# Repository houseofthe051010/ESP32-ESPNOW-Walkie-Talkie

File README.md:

Source: 

## The Project

This is a ESP32 walkie talkie that uses WIFi (ESPNOW) for long range communication. It uses the esp32-wroom-32-U with an external U.fl connector, OLED 0.96 I2C display, I2S INMP441 microphone, I2S MAX98357A 3W speaker amplifier, 10k volume potentiometer, PTT button + 5 menu buttons, LASER, and LED. The aim of this walkie talkie was to not just serve as a walkie talkie, but sort of like a custom flipper zero that was more wireless oriented, although the walkie talkie comes with 3 female dupont pins that can be plugged in externally for a UART connection.

This device was framed as a walkie talkie but it can be used as a Wi-Fi/IoT device handheld controller platform. This is the main advantage with WIFI on esp32s as you can connect to a lot of places.

### Features

* ESP-NOW DIRECT VOICE (No router needed, multiple devices can connect)
* U.FL antenna for maximum range
* Tested to 600 meters of distance
* No acknowledge on ESPNOW, just shout and listen
* 16 kHz mono voice capture with IMA ADPCM compression
* No acknowledgement can be a problem with dropped packets so at weak ranges packets are automatically duplicated
* Built in black box logging with telemetry that can be uploaded to computer.
* OLED GUI with many features to control the walkie talkie and use as a remote for other wifi things.

## Walkie Talkie Hardware

The enclosure was designed to have enough space to solder every wire, but a custom PCB version was also made, scroll all the way down to learn more about fabricating PCB.

### Electronics

* ESP32WROOM32 U.FL
* OLED I2C 0.96'
* I2S INMP441 MIC
* 10K Volume potentiometer.
* 2000 MAH LIPO
* 6 push buttons
* 5mm LED light
* 5V laser module
* Voltage divider for ADC battery voltage measurment
* Main power switch

## Assembly Process

### 1. Printed enclosure

All these parts contribute to the final product

* [`walkie_talkie_bottom_case.stl`](SOURCE%20CAD/INDIVIDUAL%20STLS/walkie_talkie_bottom_case.stl)
* [`walkie_talkie_top_cover.stl`](SOURCE%20CAD/INDIVIDUAL%20STLS/walkie_talkie_top_cover.stl)
* [`walkie_talkie_top_buttons_grid.stl`](SOURCE%20CAD/INDIVIDUAL%20STLS/walkie_talkie_top_buttons_grid.stl)
* [`walkie_talkie_OK_button.stl`](SOURCE%20CAD/INDIVIDUAL%20STLS/walkie_talkie_OK_button.stl)
* [`walkie_talkie_PTT_button.stl`](SOURCE%20CAD/INDIVIDUAL%20STLS/walkie_talkie_PTT_button.stl)
* [`walkie_talkie_PTT_button_insert.stl`](SOURCE%20CAD/INDIVIDUAL%20STLS/walkie_talkie_PTT_button_insert.stl)

### 2. Power system

The battery powers the TP4056 which gives power to a boost converter than powers the entire device

1. Wire th TP4056 through the battery to the main switch to the boost convert and then to the esp32 VIN rail.

### 3. Electronics wiring

1. To make it easy and not messy, wire every component listed in the schematic to their respected GPIO and some pins might have multiple wires to them, thats fine.
2. Make sure to use heat shrink tape to avoid short circuits. 

### 4. Front-panel assembly

1. The LED and laser press into their  holes.
2. The PTT, OK, and four navigation buttons sit in the front-panel openings.
3. Insert the OLED
4. Secure all with super glue. Make sure to apply around perimeter and not damage the electronics.

### 5. Internal packing

1. Insert the electronics. One at a type, placing the esp32 underneath the TP4056 mount, and glueing each part to their holes.
2. The enclosure has enough space to accodomate addition UART connections if you want to connect something else later on.

### 6. ESP-IDF firmware loading

1. Fork the project and config with ESP-IDF to upload the code
2. Make sure you have experience with using powershell, open it

3. Init the powershell

   ```powershell
   idf.py set-target esp32
   ```

4. Open project using

   ```powershell
   idf.py menuconfig
   ```

6. Compile using

   ```powershell
   idf.py build
   ```

7. Flash using

   ```powershell
   idf.py flash monitor
   ```

## Circuit Diagram

### Device PINOUT (Use when soldering)

| Function             | ESP32 GPIO |
| -------------------- | ---------: |
| OLED SCL             |     GPIO18 |
| OLED SDA             |     GPIO19 |
| Speaker BCLK         |     GPIO32 |
| Speaker WS/LRC       |     GPIO33 |
| Speaker DIN          |     GPIO25 |
| Microphone BCLK      |     GPIO16 |
| Microphone WS        |     GPIO17 |
| Microphone SD        |      GPIO4 |
| OK button            |      GPIO0 |
| Bottom-left button   |     GPIO14 |
| Bottom-right button  |     GPIO15 |
| Laser                |     GPIO21 |
| Volume potentiometer |     GPIO34 |
| Battery divider      |     GPIO35 |

## My versions:

## Grey Walkie

This is my 2nd iteration with much cleaner wiring

## Black Walkie

This first iteration is much more messier

### User Interface

The user interface has a whole "apps" menu for different wifi connections and button use cases, you can code your own for your own custom use cases.

### Black Box

You can debug or see what happend with the walkie in the field, this isn't really needed now that I have perfected the code though, but can be helpful if you're making your own changes.

Example of a JSON black box record:

```json
{"event":"radio_stats","t_ms":123456,"board":"BLACK","ch":1,"ptt":false,"link":true,"rssi_dbm":-82,"quality_pct":21,"jitter_frames":3,"vol_pct":50,"tx_audio":0,"tx_audio_dup":0,"tx_ctrl":2,"tx_no_mem":0,"tx_fail":0,"rx_audio":48,"rx_audio_dup":7,"rx_audio_old":0,"rx_plc":2,"rx_ctrl":1,"rx_wrong_peer":0,"rx_bad_proto":0,"rx_wrong_channel":0}
```

## Bill of Materials

| Category    | Quantity | Part                                 | Purchase Link                                                      | Estimated Price |
| ----------- | -------: | ------------------------------------ | ------------------------------------------------------------------ | --------------: |
| Fabricated  |        2 | Walkie-talkie enclosure              | [AliExpress](https://www.aliexpress.us/item/3256806989098121.html) |           $2.22 |
| Electronics |        2 | ESP32 development board              | [AliExpress](https://www.aliexpress.us/item/3256807617923920.html) |           $1.90 |
| Radio       |        2 | External antenna                     | [AliExpress](https://www.aliexpress.us/item/3256812004598286.html) |      $0.64 used |
| Display     |        2 | 0.96-inch OLED display               | [AliExpress](https://www.aliexpress.us/item/3256805954920554.html) |      $1.98 used |
| Audio       |        2 | I2S microphone                       | [AliExpress](https://www.aliexpress.us/item/3256810210666726.html) |           $6.45 |
| Audio       |        2 | I2S speaker amplifier                | [AliExpress](https://www.aliexpress.us/item/3256809715431644.html) |      $1.88 used |
| Audio       |        2 | Speaker                              | [AliExpress](https://www.aliexpress.us/item/3256805151989671.html) |           $0.99 |
| Control     |        2 | Volume potentiometer                 | [AliExpress](https://www.aliexpress.us/item/3256805703535495.html) |           $0.99 |
| Power       |        2 | Lithium battery                      | [AliExpress](https://www.aliexpress.us/item/3256811489152615.html) |     $10.96 used |
| Power       |        2 | Battery charger and protection board | [AliExpress](https://www.aliexpress.us/item/3256809139500038.html) |      $0.20 used |
| Power       |        2 | Boost converter                      | [AliExpress](https://www.aliexpress.us/item/3256811757076890.html) |      $1.88 used |
| Power       |        2 | Main power switch                    | [AliExpress](https://www.aliexpress.us/item/3256809823421130.html) |           $2.37 |
| Lighting    |        2 | Status LED                           | [AliExpress](https://www.aliexpress.us/item/3256807537207911.html) |      $0.02 used |
| Lighting    |        2 | Laser module                         | [AliExpress](https://www.aliexpress.us/item/3256808318801769.html) |           $0.99 |
| Control     |       12 | Momentary pushbutton                 | [AliExpress](https://www.aliexpress.us/item/3256810479380665.html) |           $0.99 |
| Optional RC |        2 | Continuous-rotation servo            | [AliExpress](https://www.aliexpress.us/item/3256804365417662.html) |           $9.28 |
| Measurement |        2 | 100 kΩ battery-divider resistor      | [AliExpress](https://www.aliexpress.us/item/3256802303553096.html) |      $0.02 used |
| Measurement |        2 | 220 kΩ battery-divider resistor      | [AliExpress](https://www.aliexpress.us/item/3256802303553096.html) |      $0.02 used |
| Wiring      |        1 | Signal and power wire                | [AliExpress](https://www.aliexpress.us/item/3256810394181790.html) | $0.99 allowance |

## Custom PCB Fabrication Option

If you want to avoid the hassle of soldering than fabricate your own PCB here: 

See [CUSTOM PCB FABRICATION/README.md](CUSTOM%20PCB%20FABRICATION/README.md) for the JLBPCB fabrication guide

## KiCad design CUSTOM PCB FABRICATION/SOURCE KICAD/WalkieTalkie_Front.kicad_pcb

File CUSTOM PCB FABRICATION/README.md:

# Custom PCB Fabrication

This is a KiCad PCB for those looking to make the walkie talkie from PCBs. Note that you will still have to solder some components.

## PCB Preview

Main board:

Front/user-interface board:

## Risks

Although this custom PCB works, I will be manufactering a redesigned much cleaner version later that avoids the hassle of 2 PCB boards and does everything one one, with a much slimmer walkie talkie design.

## Manufacturer Files

In this folder are the source kicad files for the PCB and manufacterable GERBER files.

### Main PCB

- [Gerber/drill ZIP](MANUFACTOR%20FILES/MAIN%20PCB/WalkieTalkie_Main_Gerbers_Drill.zip)
- [JLCPCB BOM CSV](MANUFACTOR%20FILES/MAIN%20PCB/WalkieTalkie_Main_JLCPCB_BOM.csv)
- [JLCPCB CPL / position CSV](MANUFACTOR%20FILES/MAIN%20PCB/WalkieTalkie_Main_JLCPCB_CPL.csv)

### Front PCB

- [Gerber/drill ZIP](MANUFACTOR%20FILES/FRONT%20PCB/WalkieTalkie_Front_Gerbers_Drill.zip)
- [JLCPCB BOM CSV](MANUFACTOR%20FILES/FRONT%20PCB/WalkieTalkie_Front_JLCPCB_BOM.csv)
- [JLCPCB CPL / position CSV](MANUFACTOR%20FILES/FRONT%20PCB/WalkieTalkie_Front_JLCPCB_CPL.csv)

## Parts JLCPCB Can Usually Assemble

Most of the parts and SMD components should be assembled by JLBPCB but you will need to solder these parts:

- PTT Button
- Laser module
- 10K volume potentiometer
- OLED display
- Slim 3W speaker
- Battery
- Power switch

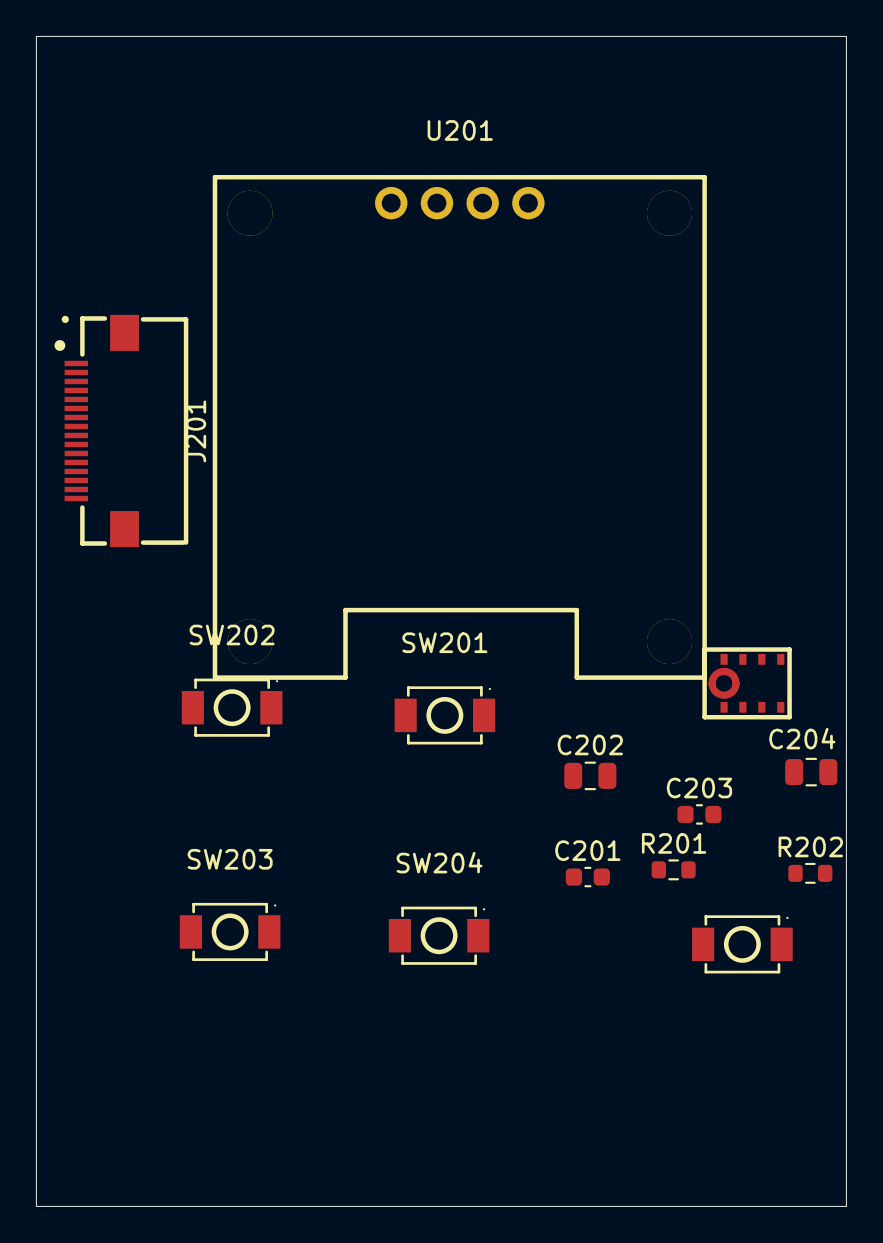
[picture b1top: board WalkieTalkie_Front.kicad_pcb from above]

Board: 2 copper layers, 45.0 x 65.0 mm, 14 parts (0 on the bottom side), 12 nets, no tracks yet.

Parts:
C201, C203: 100nF; C_0603_1608Metric
C202, C204: 10uF; C_0805_2012Metric
J201: MAIN BOARD FFC; FPC-SMD_P0.50-16P_FGS-XJ-H2.0
R201, R202: 4.7k; R_0603_1608Metric
SW201: OK; SW-SMD_L3.9-W3.0-P4.45
SW202: TOP LEFT; SW-SMD_L3.9-W3.0-P4.45
SW203: TOP RIGHT; SW-SMD_L3.9-W3.0-P4.45
SW204: BOTTOM LEFT; SW-SMD_L3.9-W3.0-P4.45
SW205: BOTTOM RIGHT; SW-SMD_L3.9-W3.0-P4.45
U201: HS96L03W2C03 0.96 OLED; OLED-TH_L27.8-W27.2-P2.54_C9900033791
U202: INMP441ACEZ; MID-SMD_L4.7-W3.8_INMP441ACEZ

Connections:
/+3V3: C201.2, C202.2, C203.2, C204.2, J201.2, J201.15, R201.2, R202.2, U201.2 (VCC), U202.7 (VDD), U202.8 (CHIPEN)
/BTN_TOP_LEFT: J201.10, SW202.1
/BTN_TOP_RIGHT: J201.11, SW203.1
/GND: C201.1, C202.1, C203.1, C204.1, J201.1, J201.3, J201.14, J201.16, J201.17, J201.18, SW201.2, SW202.2, SW203.2, SW204.2, SW205.2, U201.1 (GND), U202.4 (L/R), U202.5 (GND), U202.6 (GND), U202.9 (GND)
/GPIO0_BTN_OK: J201.9, SW201.1
/GPIO4_MIC_SD: J201.8, U202.2 (SD)
/GPIO14_BTN_BOTTOM_LEFT: J201.12, SW204.1
/GPIO15_BTN_BOTTOM_RIGHT: J201.13, SW205.1
/GPIO16_MIC_BCLK: J201.6, U202.1 (SCK)
/GPIO17_MIC_WS: J201.7, U202.3 (WS)
/GPIO18_OLED_SCL: J201.4, R201.1, U201.3 (SCL)
/GPIO19_OLED_SDA: J201.5, R202.1, U201.4 (SDA)

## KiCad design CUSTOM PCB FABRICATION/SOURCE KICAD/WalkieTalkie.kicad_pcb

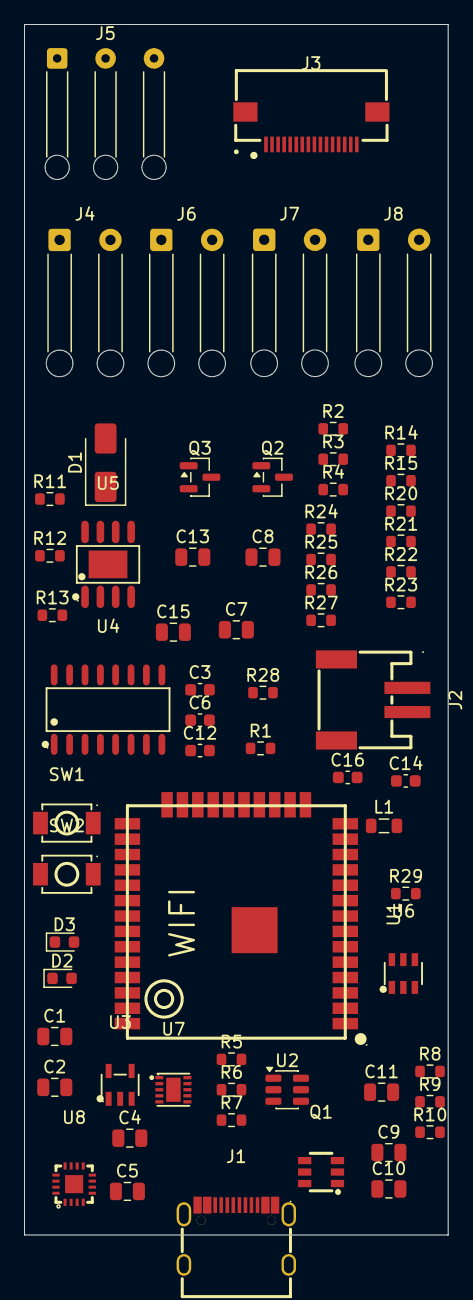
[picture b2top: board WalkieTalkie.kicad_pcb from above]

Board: 2 copper layers, 35.0 x 100.0 mm, 66 parts (0 on the bottom side), 57 nets, no tracks yet.

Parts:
C1, C2, C11: 1uF; C_0805_2012Metric
C3, C6, C12, C14, C16: 100nF; C_0603_1608Metric
C4, C5, C7, C8, C9, C10, C13, C15: 10uF; C_0805_2012Metric
D1: SS34; D_SMA
D2: RED CHARGING; LED_0603_1608Metric
D3: GREEN FULL; LED_0603_1608Metric
J1: TYPE-C-31-M-12; USB-C_SMD-TYPE-C-31-M-12_1
J2: BATTERY JST-PH; CONN-SMD_P2.00_S2B-PH-SM4-TB-LF-SN
J3: FRONT BOARD FFC; FPC-SMD_P0.50-16P_FGS-XJ-H2.0
J4: SPEAKER WIRES; SolderWire-0.25sqmm_1x02_P4.2mm_D0.65mm_OD1.7mm_Relief
J5: 10k POTENTIOMETER; SolderWire-0.15sqmm_1x03_P4mm_D0.5mm_OD1.5mm_Relief
J6: PTT BUTTON; SolderWire-0.25sqmm_1x02_P4.2mm_D0.65mm_OD1.7mm_Relief
J7: EXTERNAL LED; SolderWire-0.25sqmm_1x02_P4.2mm_D0.65mm_OD1.7mm_Relief
J8: LASER WIRES; SolderWire-0.25sqmm_1x02_P4.2mm_D0.65mm_OD1.7mm_Relief
L1: 2.2uH >=2A; L_0805_2012Metric
Q1: FS8205A; SOT-23-6_L2.9-W1.6-P0.95-LS2.8-BR
Q2: AO3401A; SOT-23
Q3: AO3400A; SOT-23
R1, R2: 5.1k; R_0603_1608Metric
R3: 2.4k (500mA); R_0603_1608Metric
R4, R5, R7: 1k; R_0603_1608Metric
R6: 100R; R_0603_1608Metric
R8, R10, R11: 10k; R_0603_1608Metric
R9, R12, R15: 100k; R_0603_1608Metric
R13: 1M; R_0603_1608Metric
R14: 330R; R_0603_1608Metric
R20, R21, R22, R23: 0R BLACK; R_0603_1608Metric
R24, R25, R26, R27: 0R GREY; R_0603_1608Metric
R28, R29: 220k; R_0603_1608Metric
SW1: RESET; SW-SMD_L3.9-W3.0-P4.45
SW2: BOOT; SW-SMD_L3.9-W3.0-P4.45
U1: ESP32-WROOM-32U-N4; WIFIM-SMD_38P-L19.2-W18.0-P1.27
U2: USBLC6-2SC6; SOT-23-6
U3: ME6211C33M5G-N; SOT-23-5_L3.0-W1.7-P0.95-LS2.8-BL
U4: CH340C; SOP-16_L10.0-W3.9-P1.27-LS6.0-BL
U5: TP4056; ESOP-8_L4.9-W3.9-P1.27-LS6.0-BL-EP-4
U6: DW01A; SOT-23-6_L2.9-W1.6-P0.95-LS2.8-BL
U7: TPS63031DSKR; SON-10_L2.5-W2.5-P0.50-TL-EP
U8: MAX98357AETE+T; TQFN-16_L3.0-W3.0-P0.50-BL-EP1.5

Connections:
/+3V3: C9.2, C10.2, C12.2, C13.2, J3.2, J3.15, J5.1, J8.1, R10.2, R11.2, U1.2 (3V3), U7.1 (VOUT), U7.10 (FB)
/+3V3_USB: C2.2, C3.2, U3.5 (VOUT), U4.4 (V3), U4.16 (VCC)
/AMP_GAIN: R12.2, U8.2 (GAIN_SLOT)
/AMP_SD_MODE: R13.2, U8.4 (~SD_MODE)
/BAT_POS: C5.2, J2.1, Q2.2 (S), R6.2, R28.2, U5.5 (BAT)
/BAT_RAW_N: C6.1, J2.2, Q1.1 (S1), U6.6 (GND)
/BB_L1: L1.2, U7.4 (L1)
/BB_L2: L1.1, U7.2 (L2)
/BTN_TOP_LEFT: J3.10, R22.1, R26.1
/BTN_TOP_RIGHT: J3.11, R23.1, R27.1
/DW_VCC: C6.2, R6.1, U6.5 (VCC)
/DW_VM: R7.2, U6.2 (VM)
/ESP_EN: C11.2, R10.1, SW1.1, U1.3 (EN)
/GND: C1.1, C2.1, C3.1, C4.1, C5.1, C7.1, C8.1, C9.1, C10.1, C11.1, C12.1, C13.1, C14.1, C15.1, C16.1, J1.1 (EH), J1.2 (EH), J1.3 (EH), J1.4 (EH), J1.A1B12 (GND), J1.B1A12 (GND), J2.3, J2.4, J3.1, J3.3, J3.14, J3.16, J3.17, J3.18, J5.3, J6.2, J7.2, Q1.3 (S2), Q3.2 (S), R1.1, R2.1, R3.1, R7.1, R9.1, R12.1, R15.1, R29.1, SW1.2, SW2.2, U1.1 (GND), U1.15 (GND), U1.38 (GND), U1.39 (GND), U2.2 (GND), U3.2 (VSS), U4.1 (GND), U4.15 (R232), U5.1 (TEMP), U5.3 (GND), U5.9 (PAD), U6.4 (TD), U7.3 (PGND), U7.7 (PS/SYNC), U7.9 (GND), U7.11 (EP), U8.3 (GND), U8.11 (GND), U8.15 (GND), U8.17 (EP)
/GPIO0_BTN_OK: J3.9, R11.1, SW2.1, U1.25 (IO0)
/GPIO2: R23.2, R26.2, U1.24 (IO2)
/GPIO4_MIC_SD: J3.8, U1.26 (IO4)
/GPIO14_BTN_BOTTOM_LEFT: J3.12, U1.13 (IO14)
/GPIO15_BTN_BOTTOM_RIGHT: J3.13, U1.23 (IO15)
/GPIO16_MIC_BCLK: J3.6, U1.27 (IO16)
/GPIO17_MIC_WS: J3.7, U1.28 (IO17)
/GPIO18_OLED_SCL: J3.4, U1.30 (IO18)
/GPIO19_OLED_SDA: J3.5, U1.31 (IO19)
/GPIO21_LASER: Q3.1 (G), R15.2, U1.33 (IO21)
/GPIO22: R20.2, R25.2, U1.36 (IO22)
/GPIO23: R21.2, R24.2, U1.37 (IO23)
/GPIO25_SPK_DIN: U1.10 (IO25), U8.1 (DIN)
/GPIO26: R22.2, R27.2, U1.11 (IO26)
/GPIO32_SPK_BCLK: U1.8 (IO32), U8.16 (BCLK)
/GPIO33_SPK_LRC: U1.9 (IO33), U8.14 (LRCLK)
/GPIO34_VOLUME: J5.2, U1.6 (IO34)
/GPIO35_BATTERY: C16.2, R28.1, R29.2, U1.7 (IO35)
/LASER_NEG: J8.2, Q3.3 (D)
/LED_CHRG_A: D2.1 (K), R4.1
/LED_CTRL: R14.2, R21.1, R25.1
/LED_DONE_A: D3.1 (K), R5.1
/LED_EXT_ANODE: J7.1, R14.1
/LOAD_GATE: Q2.1 (G), R8.1, R9.2
/MOS_MID: Q1.2 (D1/D2), Q1.5 (D1/D2)
/PROTECT_OC: Q1.4 (G2), U6.3 (OC)
/PROTECT_OD: Q1.6 (G1), U6.1 (OD)
/PTT: J6.1, R20.1, R24.1
/SPK_MINUS: J4.2, U8.10 (OUTN)
/SPK_PLUS: J4.1, U8.9 (OUTP)
/TP_CHRG: D2.2 (A), U5.7 (CHRG)
/TP_PROG: R3.2, U5.2 (PROG)
/TP_STDBY: D3.2 (A), U5.6 (STDBY)
/UART_RX0: U1.34 (RXD0), U4.2 (TXD)
/UART_TX0: U1.35 (TXD0), U4.3 (RXD)
/USB_CC1: J1.A5 (CC1), R1.2
/USB_CC2: J1.B5 (CC2), R2.2
/USB_DN: U2.6 (I/O1), U4.6 (D-)
/USB_DN_CONN: J1.A7 (DN1), J1.B7 (DN2), U2.1 (I/O1)
/USB_DP: U2.4 (I/O2), U4.5 (D+)
/USB_DP_CONN: J1.A6 (DP1), J1.B6 (DP2), U2.3 (I/O2)
/USB_VBUS: C1.2, C4.2, D1.2 (A), J1.A4B9 (VBUS), J1.B4A9 (VBUS), R4.2, R5.2, R8.2, U2.5 (VBUS), U3.1 (VIN), U3.3 (CE), U5.4 (VCC), U5.8 (CE)
/VSYS: C7.2, C8.2, C14.2, C15.2, D1.1 (K), Q2.3 (D), R13.1, U7.5 (VIN), U7.6 (EN), U7.8 (VINA), U8.7 (VDD), U8.8 (VDD)

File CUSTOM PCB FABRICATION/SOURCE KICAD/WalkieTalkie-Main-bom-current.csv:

"Refs","Value","Footprint","MPN","LCSC","DNP"
"C1,C2,C11","1uF","Capacitor_SMD:C_0805_2012Metric","","",""
"C3,C6,C12,C14,C16","100nF","Capacitor_SMD:C_0603_1608Metric","","",""
"C4,C5,C7-C10,C13,C15","10uF","Capacitor_SMD:C_0805_2012Metric","","",""
"D1","SS34","Diode_SMD:D_SMA","SS34","C8678",""
"D2","RED CHARGING","LED_SMD:LED_0603_1608Metric","","",""
"D3","GREEN FULL","LED_SMD:LED_0603_1608Metric","","",""
"J1","TYPE-C-31-M-12","WalkieTalkie_JLCPCB:USB-C_SMD-TYPE-C-31-M-12_1","TYPE-C-31-M-12","C165948",""
"J2","BATTERY JST-PH","WalkieTalkie_JLCPCB:CONN-SMD_P2.00_S2B-PH-SM4-TB-LF-SN","S2B-PH-SM4-TB(LF)(SN)","C295747",""
"J3","FRONT BOARD FFC","WalkieTalkie_JLCPCB:FPC-SMD_P0.50-16P_FGS-XJ-H2.0","AFC01-S16FCC-00","C262272",""
"J4","SPEAKER WIRES","Connector_Wire:SolderWire-0.25sqmm_1x02_P4.2mm_D0.65mm_OD1.7mm_Relief","","",""
"J5","10k POTENTIOMETER","Connector_Wire:SolderWire-0.15sqmm_1x03_P4mm_D0.5mm_OD1.5mm_Relief","","",""
"J6","PTT BUTTON","Connector_Wire:SolderWire-0.25sqmm_1x02_P4.2mm_D0.65mm_OD1.7mm_Relief","","",""
"J7","EXTERNAL LED","Connector_Wire:SolderWire-0.25sqmm_1x02_P4.2mm_D0.65mm_OD1.7mm_Relief","","",""
"J8","LASER WIRES","Connector_Wire:SolderWire-0.25sqmm_1x02_P4.2mm_D0.65mm_OD1.7mm_Relief","","",""
"L1","2.2uH >=2A","Inductor_SMD:L_0805_2012Metric","","",""
"Q1","FS8205A","WalkieTalkie_JLCPCB:SOT-23-6_L2.9-W1.6-P0.95-LS2.8-BR","FS8205A","C2830320",""
"Q2","AO3401A","Package_TO_SOT_SMD:SOT-23","AO3401A","C15127",""
"Q3","AO3400A","Package_TO_SOT_SMD:SOT-23","AO3400A","C20917",""
"R1,R2","5.1k","Resistor_SMD:R_0603_1608Metric","","","No"
"R3","2.4k (500mA)","Resistor_SMD:R_0603_1608Metric","","","No"
"R4,R5,R7","1k","Resistor_SMD:R_0603_1608Metric","","","No"
"R6","100R","Resistor_SMD:R_0603_1608Metric","","","No"
"R8,R10,R11","10k","Resistor_SMD:R_0603_1608Metric","","","No"
"R9,R12,R15","100k","Resistor_SMD:R_0603_1608Metric","","","No"
"R13","1M","Resistor_SMD:R_0603_1608Metric","","","No"
"R14","330R","Resistor_SMD:R_0603_1608Metric","","","No"
"R20-R23","0R BLACK","Resistor_SMD:R_0603_1608Metric","","","No"
"R24-R27","0R GREY","Resistor_SMD:R_0603_1608Metric","","","Yes"
"R28,R29","220k","Resistor_SMD:R_0603_1608Metric","","","No"
"SW1","RESET","WalkieTalkie_JLCPCB:SW-SMD_L3.9-W3.0-P4.45","TS-1088R-02026","C455280",""
"SW2","BOOT","WalkieTalkie_JLCPCB:SW-SMD_L3.9-W3.0-P4.45","TS-1088R-02026","C455280",""
"U1","ESP32-WROOM-32U-N4","WalkieTalkie_JLCPCB:WIFIM-SMD_38P-L19.2-W18.0-P1.27","ESP32-WROOM-32U-N4","C328062",""
"U2","USBLC6-2SC6","Package_TO_SOT_SMD:SOT-23-6","USBLC6-2SC6","C7519",""
"U3","ME6211C33M5G-N","WalkieTalkie_JLCPCB:SOT-23-5_L3.0-W1.7-P0.95-LS2.8-BL","ME6211C33M5G-N","C82942",""
"U4","CH340C","WalkieTalkie_JLCPCB:SOP-16_L10.0-W3.9-P1.27-LS6.0-BL","CH340C","C84681",""
"U5","TP4056","WalkieTalkie_JLCPCB:ESOP-8_L4.9-W3.9-P1.27-LS6.0-BL-EP-4","TP4056","C20199357",""
"U6","DW01A","WalkieTalkie_JLCPCB:SOT-23-6_L2.9-W1.6-P0.95-LS2.8-BL","DW01A","C351410",""
"U7","TPS63031DSKR","WalkieTalkie_JLCPCB:SON-10_L2.5-W2.5-P0.50-TL-EP","TPS63031DSKR","C15516",""
"U8","MAX98357AETE+T","WalkieTalkie_JLCPCB:TQFN-16_L3.0-W3.0-P0.50-BL-EP1.5","MAX98357AETE+T","C910544",""
